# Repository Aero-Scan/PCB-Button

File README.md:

# AeroScan - Wireless Network Q&P Monitoring - PCB Button

## Overview

AeroScan is an IoT-based system designed to monitor the Quality and Performance (Q&P) of wireless network infrastructure. This project utilizes Raspberry Pi devices deployed across a site to collect real-time network metrics. These metrics are then sent to a central server for aggregation by Prometheus and visualization via Grafana dashboards, providing valuable insights into network health, helping to identify potential issues, and ensuring a reliable wireless experience.

The system features a central registration service (`pi-registrar`) for dynamic discovery of Raspberry Pi nodes by Prometheus. Configuration of the Raspberry Pis, including sensitive details like WiFi credentials and API keys, can be managed remotely using Ansible from the central server.

## Usage

*   **Ordering** Order PCB from a Pcb manufacturing and parts Through hole parts.
*   **Assembly** Assemble according to KiCAD designs.
*   **How Too** Attach button PCB to GPIO Pins on the PI and press both buttons at the same time to generate a new Unique Identifier.

## License

AeroScan is licensed under the **Creative Commons Attribution-NonCommercial-ShareAlike 4.0 International License (CC BY-NC-SA 4.0)**.

You are free to **share** (copy and redistribute the material in any medium or format) and **adapt** (remix, transform, and build upon the material) under the following terms:

*   **Attribution** — You must give [appropriate credit](https://creativecommons.org/licenses/by-nc-sa/4.0/#ref-appropriate-credit), provide a link to the license, and [indicate if changes were made](https://creativecommons.org/licenses/by-nc-sa/4.0/#ref-indicate-changes). You may do so in any reasonable manner, but not in any way that suggests the licensor endorses you or your use.
*   **NonCommercial** — You may not use the material for [commercial purposes](https://creativecommons.org/licenses/by-nc-sa/4.0/#ref-commercial-purposes).
*   **ShareAlike** - If you remix, transform, or build upon the material, you must distribute your contributions under the [same license](https://creativecommons.org/licenses/by-nc-sa/4.0/#ref-same-license) as the original.
*   **No additional restrictions** — You may not apply legal terms or [technological measures](https://creativecommons.org/licenses/by-nc-sa/4.0/#ref-technological-measures) that legally restrict others from doing anything the license permits.

For more information, see the [full license text](LICENSE) in this repository or visit:
[https://creativecommons.org/licenses/by-nc-sa/4.0/](https://creativecommons.org/licenses/by-nc-sa/4.0/)

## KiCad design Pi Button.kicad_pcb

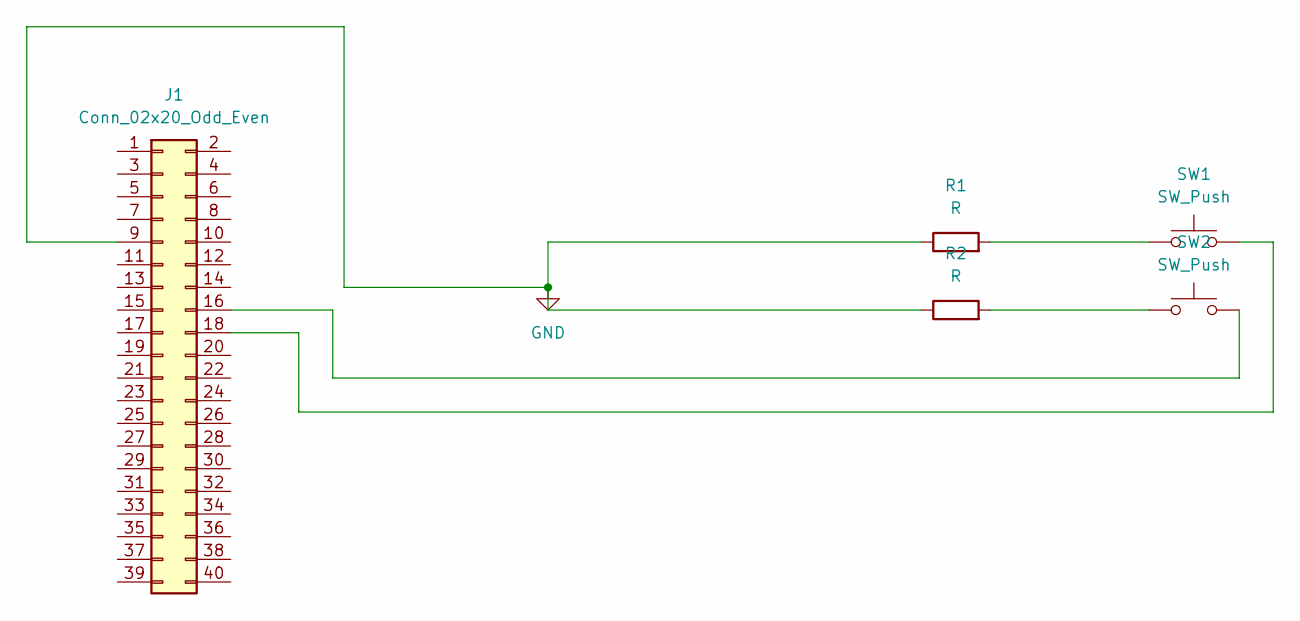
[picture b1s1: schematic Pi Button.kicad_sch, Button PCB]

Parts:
J1: Conn_02x20_Odd_Even; PinSocket_2x20_P2.54mm_Vertical
R1, R2: R; R_Axial_DIN0204_L3.6mm_D1.6mm_P2.54mm_Vertical
SW1, SW2: SW_Push; SW_PUSH_6mm_H9.5mm

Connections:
GND: J1.9, R1.1, R2.1
unnamed: J1.16, SW2.2
unnamed: J1.18, SW1.2
unnamed: R1.2, SW1.1
unnamed: R2.2, SW2.1

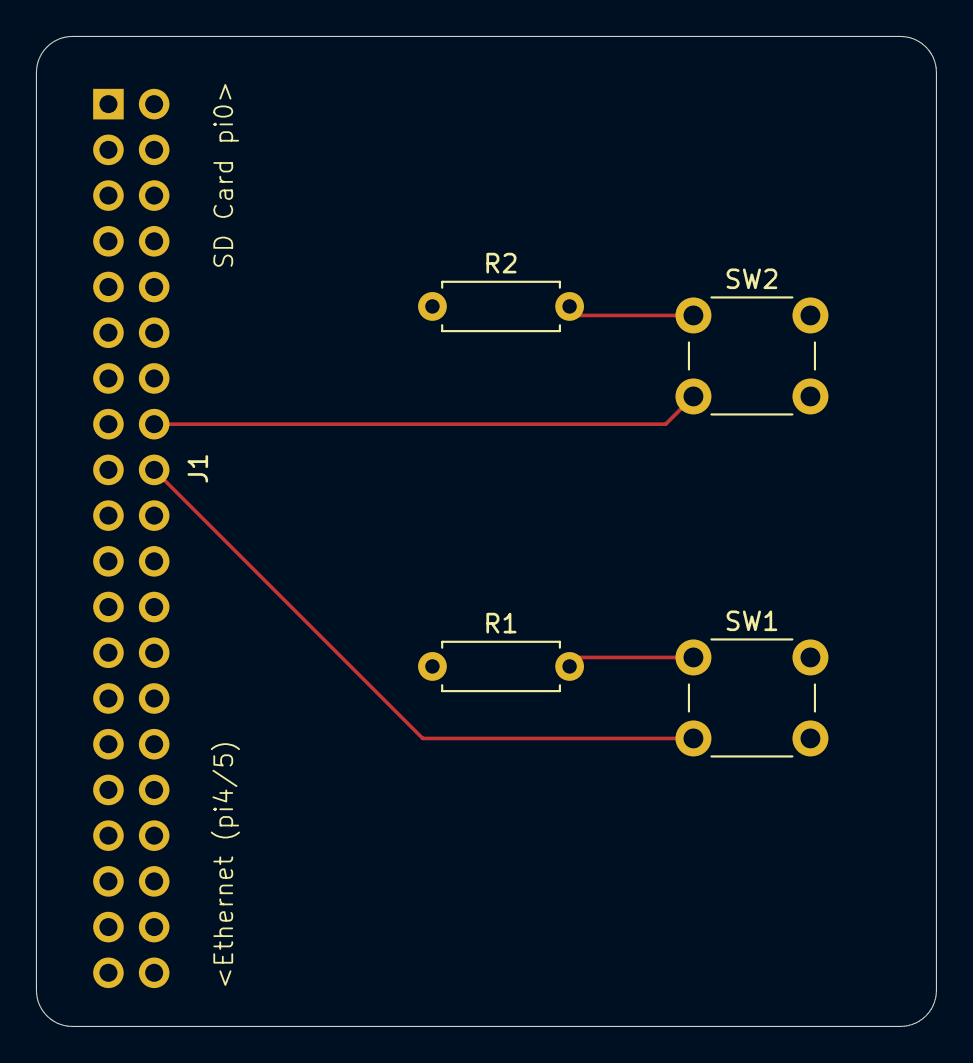
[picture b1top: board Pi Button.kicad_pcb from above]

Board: 2 copper layers, 50.0 x 55.0 mm, 5 parts (1 on the bottom side), 5 nets.

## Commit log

2025-04-21 First commit of pi PCB
2025-04-21 pi pcb
2025-04-21 prelim PCB
2025-04-21 change to traced files
2025-04-22 part placement
2025-04-22 removed unnessasary files
2025-04-22 remove backups directory
2025-05-01 added .gitignore
2025-05-01 changed resistors and silk screen
2025-05-01 rounded corners of pcb
2025-05-01 update to .gitignore and other files
2025-05-27 Added LICENCE
2025-05-27 Update to README
